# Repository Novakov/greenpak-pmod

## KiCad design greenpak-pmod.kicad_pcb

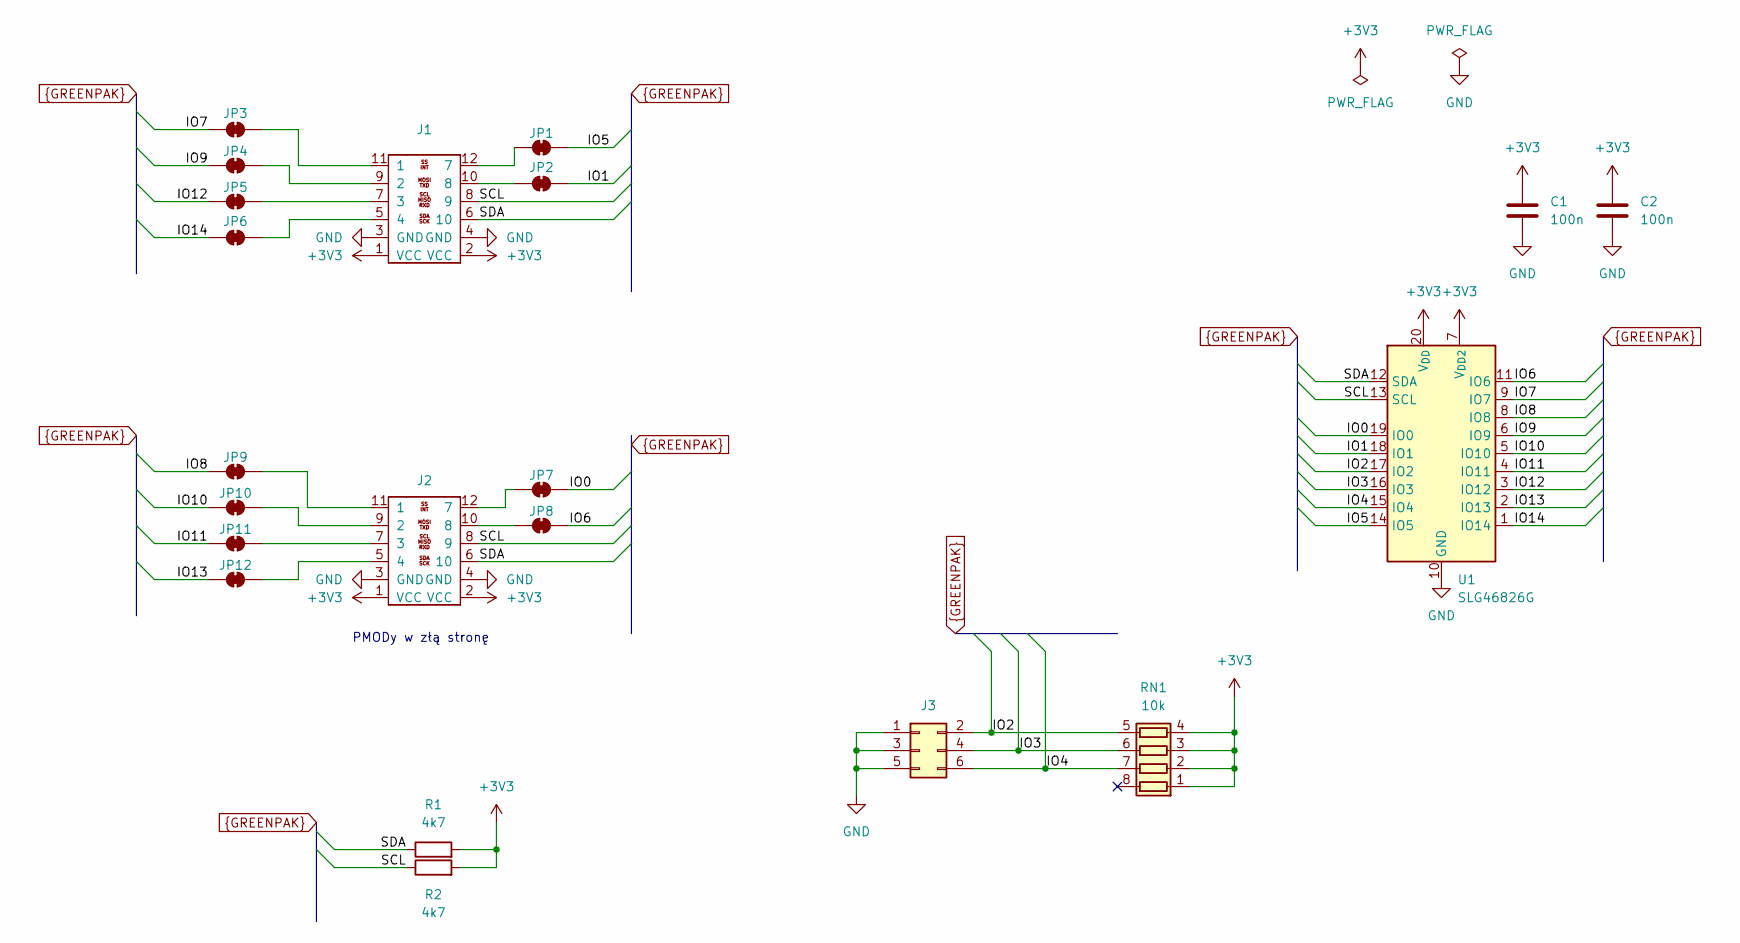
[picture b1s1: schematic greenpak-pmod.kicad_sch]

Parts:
C1, C2: 100n; C_0805_2012Metric_Pad1.18x1.45mm_HandSolder
J1: PinHeader_2x06_P2.54mm_Horizontal
J2: Conn_02x06_Top_Bottom; PinSocket_2x06_P2.54mm_Horizontal
J3: Conn_02x03_Counter_Clockwise; PinHeader_2x03_P1.27mm_Vertical_SMD
JP1: SolderJumper-2_P1.3mm_Bridged_Pad1.0x1.5mm
JP2, JP3, JP4, JP5, JP6, JP7, JP8, JP9, JP10, JP11, JP12: SolderJumper_2_Bridged; SolderJumper-2_P1.3mm_Bridged_Pad1.0x1.5mm
R1, R2: 4k7; R_0603_1608Metric_Pad0.98x0.95mm_HandSolder
RN1: 10k; R_Array_Convex_4x0603
U1: SLG46826G; TSSOP-20_4.4x6.5mm_P0.65mm

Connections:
+3V3: C1.1, C2.1, J1.1 (VCC), J1.2 (VCC), J2.1 (VCC), J2.2 (VCC), R1.2, R2.2, RN1.1 (R1.1), RN1.2 (R2.1), RN1.3 (R3.1), RN1.4 (R4.1), U1.7 (V_{DD2}), U1.20 (V_{DD})
GND: C1.2, C2.2, J1.3 (GND), J1.4 (GND), J2.3 (GND), J2.4 (GND), J3.1, J3.3, J3.5, U1.10 (GND)
IO0: JP7.2 (B), U1.19 (IO0)
IO1: JP2.2 (B), U1.18 (IO1)
IO2: J3.2, RN1.5 (R4.2), U1.17 (IO2)
IO3: J3.4, RN1.6 (R3.2), U1.16 (IO3)
IO4: J3.6, RN1.7 (R2.2), U1.15 (IO4)
IO5: JP1.2 (B), U1.14 (IO5)
IO6: JP8.2 (B), U1.11 (IO6)
IO7: JP3.1 (A), U1.9 (IO7)
IO8: JP9.1 (A), U1.8 (IO8)
IO9: JP4.1 (A), U1.6 (IO9)
IO10: JP10.1 (A), U1.5 (IO10)
IO11: JP11.1 (A), U1.4 (IO11)
IO12: JP5.1 (A), U1.3 (IO12)
IO13: JP12.1 (A), U1.2 (IO13)
IO14: JP6.1 (A), U1.1 (IO14)
unnamed: J1.11 (1), JP3.2 (B)
unnamed: J1.9 (2), JP4.2 (B)
unnamed: J1.7 (3), JP5.2 (B)
unnamed: J1.5 (4), JP6.2 (B)
unnamed: J1.12 (7), JP1.1 (A)
unnamed: J1.10 (8), JP2.1 (A)
unnamed: J2.11 (1), JP9.2 (B)
unnamed: J2.9 (2), JP10.2 (B)
unnamed: J2.7 (3), JP11.2 (B)
unnamed: J2.5 (4), JP12.2 (B)
unnamed: J2.12 (7), JP7.1 (A)
unnamed: J2.10 (8), JP8.1 (A)
SCL: J1.8 (9), J2.8 (9), R2.1, U1.13 (SCL)
SDA: J1.6 (10), J2.6 (10), R1.1, U1.12 (SDA)

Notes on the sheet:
PMODy w złą stronę

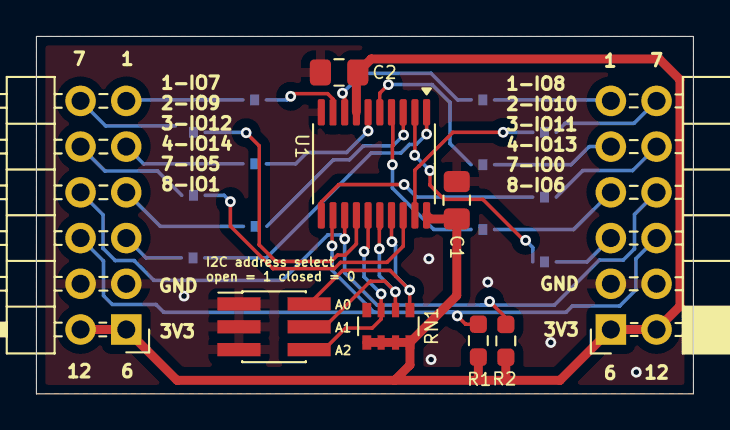
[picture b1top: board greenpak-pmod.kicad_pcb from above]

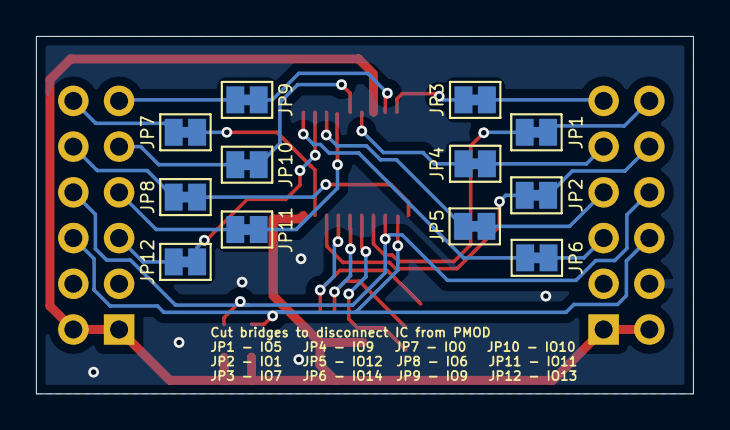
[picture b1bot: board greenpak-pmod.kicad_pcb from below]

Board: 2 copper layers, 36.5 x 19.9 mm, 21 parts (12 on the bottom side), 31 nets.
